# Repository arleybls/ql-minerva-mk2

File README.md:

# Sinclair QL - Minerva MK II Reimagined (SMD edition)

A surface-mount redesign of the Minerva MK II ROM and clock board for the Sinclair QL, based on
[Alvaro Alea Fernandez's KiCad recreation](https://github.com/alvaroalea/QL_Minerva_MK2) of the
original 1990 QView board.

The board plugs into the QL's internal ROM socket. It replaces the QL's ROM with a 64 KB EPROM
holding the Minerva operating system, with Toolkit II in the upper 16 KB if you want it, and adds
a battery-backed PCF8583 real-time clock. The clock sits on an I2C port inside the ROM address
space, so the QL reads it with ordinary ROM reads.

Left: the assembled board. Right: with the I2C cable plugged into J2.

## What is different from Alvaro's board

| | Alvaro's board | This board |
|---|---|---|
| Construction | through-hole | surface mount, 42.7 x 40.6 mm, two layers, ground pour on each side |
| EPROM | W27C512, DIP-28 socket, with the 74LS133 soldered underneath it | 27C512 in a PLCC-32 SMD socket; nothing mounted under anything |
| GAL16V8 | DIP-20 socket | PLCC-20 SMD socket, still reprogrammable |
| 13-input NAND | 74LS133, DIP-16 | SN74ALS133, SOP-16 |
| Resistors, diode, crystal, trimmer | axial, DO-35, AT310, radial trimmer | 0603, SOD-123W, FC-135, TZC3 SMD trimmer |
| Expansion header J2 | 2.54 mm pins | PicoBlade 53261 |
| Battery | external, through a two-pin header and a 120 ohm trickle-charge resistor | CR927 coin cell on the board, fed through two Schottky diodes so the cell is never charged and takes over when the QL is off |
| GAL pins 6 and 7 | pin 6 on VCC, pin 7 on /DECODE | pin 6 on SW1, pin 7 on +5 V, as the MINGAL_MH v1.10 equations require; this makes the map-in/map-out of the upper 16 KB work |
| Upper 16 KB select | JP1 solder jumper | SW1 slide switch (see below) |
| Decoupling | two capacitors | four 100 nF: at the GAL, the 74ALS133 and the EPROM on +5 V, and one at the PCF8583 on the battery rail |
| Clock chip testing | none | a small tester board and sketch (see below) |

### A switch instead of a solder jumper

Upstream JP1 was a three-pad solder jumper with its centre pad on the /DECODE net, which is the
74LS133's output. Pads 1 and 2 were bridged by default, so the jumper shorted that output to the
supply. SW1, a slide switch on its own GAL input, replaces it. SW1 selects whether the EPROM's
upper 16 KB (Toolkit II) is mapped in or left free for an external expansion ROM.

### A tester for the clock chips

`pcf8583-tester/` is a small separate board (Arduino Nano plus a DIP-8 socket) and a sketch for
checking PCF8583 chips before one is soldered in. It writes ten test patterns to all 248 bytes
of RAM, checks the clock registers, then drives the chip's oscillator input from the Nano at 100
times real speed to run the whole counter chain: minute, hour, month, leap-year rollovers, the
alarm and the timer. It prints a checklist and a pass or fail verdict in about three seconds.
Second-hand and old-stock PCF8583s vary a lot in quality, and this finds the bad ones. See
[pcf8583-tester/README.md](pcf8583-tester/README.md).

## Repository layout

```
QL_Minerva_MK2.kicad_sch / .kicad_pcb / .kicad_pro   the board (KiCad 10)
gerber/                                              fabrication files for the current board
bom/ibom.html                                        interactive BOM
images/                                              photos
pcf8583-tester/                                      clock chip tester: KiCad project, gerbers, sketch, README
```

The ROM image and the GAL files are not in this repository. They are the work of their
original authors; the next two sections say where to get them and how to prepare them.

## Getting the GAL code

The GAL16V8 needs the MINGAL_MH v1.10 fuse map (`MINGAL_MH_v110.jed`). Alvaro's README says
where his copy came from:

> Main information, GAL code, pictures, etc... has been obtained from this post:
> https://qlforum.co.uk/viewtopic.php?t=1993

That thread on qlforum.co.uk has the JEDEC file, the equations and the history of the v1.00
and v1.10 versions. Program the `.jed` into a GAL16V8 (or an ATF16V8) with any GAL programmer,
for example a TL866 with minipro or Xgpro.

## Building the ROM image with Toolkit II

The 27C512 holds a 1:1 image of the QL's ROM area:

```
0x0000-0xBFFF   Minerva 1.98a1 operating system (48 KB)
0xC000-0xFFFF   Toolkit II 2.36 (16 KB), in the QL's expansion ROM slot
```

The 64 KB image is nothing more than the two files joined, Minerva first.

1. Get Minerva 1.98a1 (the 48 KB ROM file) from Tony Firshman's Minerva page:
   http://tfs.firshman.co.uk/ql/minerva.htm
2. Get the Toolkit II v2.36 ROM image (16 KB) from Dilwyn Jones' site:
   https://dilwyn.qlforum.co.uk/docs/manuals/index.html (Toolkit II section).
3. Check the sizes: Minerva must be exactly 49,152 bytes and Toolkit II 16,384 bytes.
   If the Toolkit II file is shorter, pad it with 0xFF to 16,384 bytes.
4. Join them.

   Linux or macOS:

   ```
   cat Minerva_1.98a1.bin TK2_2.36.rom > Minerva_1.98a1_plus_TK2_2.36.bin
   ```

   Windows (PowerShell):

   ```
   cmd /c copy /b Minerva_1.98a1.bin+TK2_2.36.rom Minerva_1.98a1_plus_TK2_2.36.bin
   ```

   The result must be exactly 65,536 bytes.
5. Burn the 64 KB file into the 27C512 and set SW1 so the upper 16 KB is mapped in.

If you do not want Toolkit II, burn the 48 KB Minerva file on its own (the programmer fills the
rest of the EPROM with 0xFF) and set SW1 so the upper 16 KB is left free for an expansion ROM.

The last four bytes of the Minerva image (0xBFDC-0xBFDF) are the clock's I2C window. The GAL
intercepts reads there, so whatever the EPROM holds at those addresses is never seen; Minerva
reserves them for this purpose.

## Building one

1. Order the board from `gerber/`.
2. Fit the SMD parts, the two PLCC sockets and the CR927 holder. U1 is a 28-pin header row
   mounted on the solder side so the board can be plugged into the QL's ROM socket.
3. Program a GAL16V8 with `MINGAL_MH_v110.jed` and a 27C512 with the Minerva image, with or
   without Toolkit II (see the two sections above).
4. If the PCF8583 is not a new part, run it through the tester first, then fit it.
5. Set SW1: Toolkit II mapped in (64 KB image), or upper 16 KB left free for an expansion ROM.
6. Fit the cell, plug the board into the QL's ROM socket and power up.

## Licence

CERN Open Hardware Licence Version 2, Strongly Reciprocal (CERN-OHL-S v2), the same licence
as Alvaro's repository. The full text is in [LICENSE](LICENSE). The Minerva MK II design, the
Minerva OS and the GAL equations remain the work of their original authors. This repository
only carries the redesigned board.

Board redesign and tester (c) 2026 Arley Silveira. KiCad capture of the original (c) 2024
Alvaro Alea Fernandez.

Source location: https://github.com/arleybls/ql-minerva-mk2

Modification notice (CERN-OHL-S 3.3b): in 2025-2026 Arley Silveira converted Alvaro Alea
Fernandez's through-hole design to surface mount, added the on-board battery, rewired GAL pins
6 and 7, replaced JP1 with SW1, added decoupling and wrote the PCF8583 tester.

## References

- Alvaro's repository: https://github.com/alvaroalea/QL_Minerva_MK2
- Minerva at Tony Firshman's site: http://tfs.firshman.co.uk/ql/minerva.htm
- Minerva on the QL wiki: https://wiki.qlforum.co.uk/doku.php?id=qlwiki:minerva
- Manuals and software: https://dilwyn.qlforum.co.uk/docs/manuals/index.html
- Minerva MK II forum thread with the GAL code, pictures and history: https://qlforum.co.uk/viewtopic.php?t=1993

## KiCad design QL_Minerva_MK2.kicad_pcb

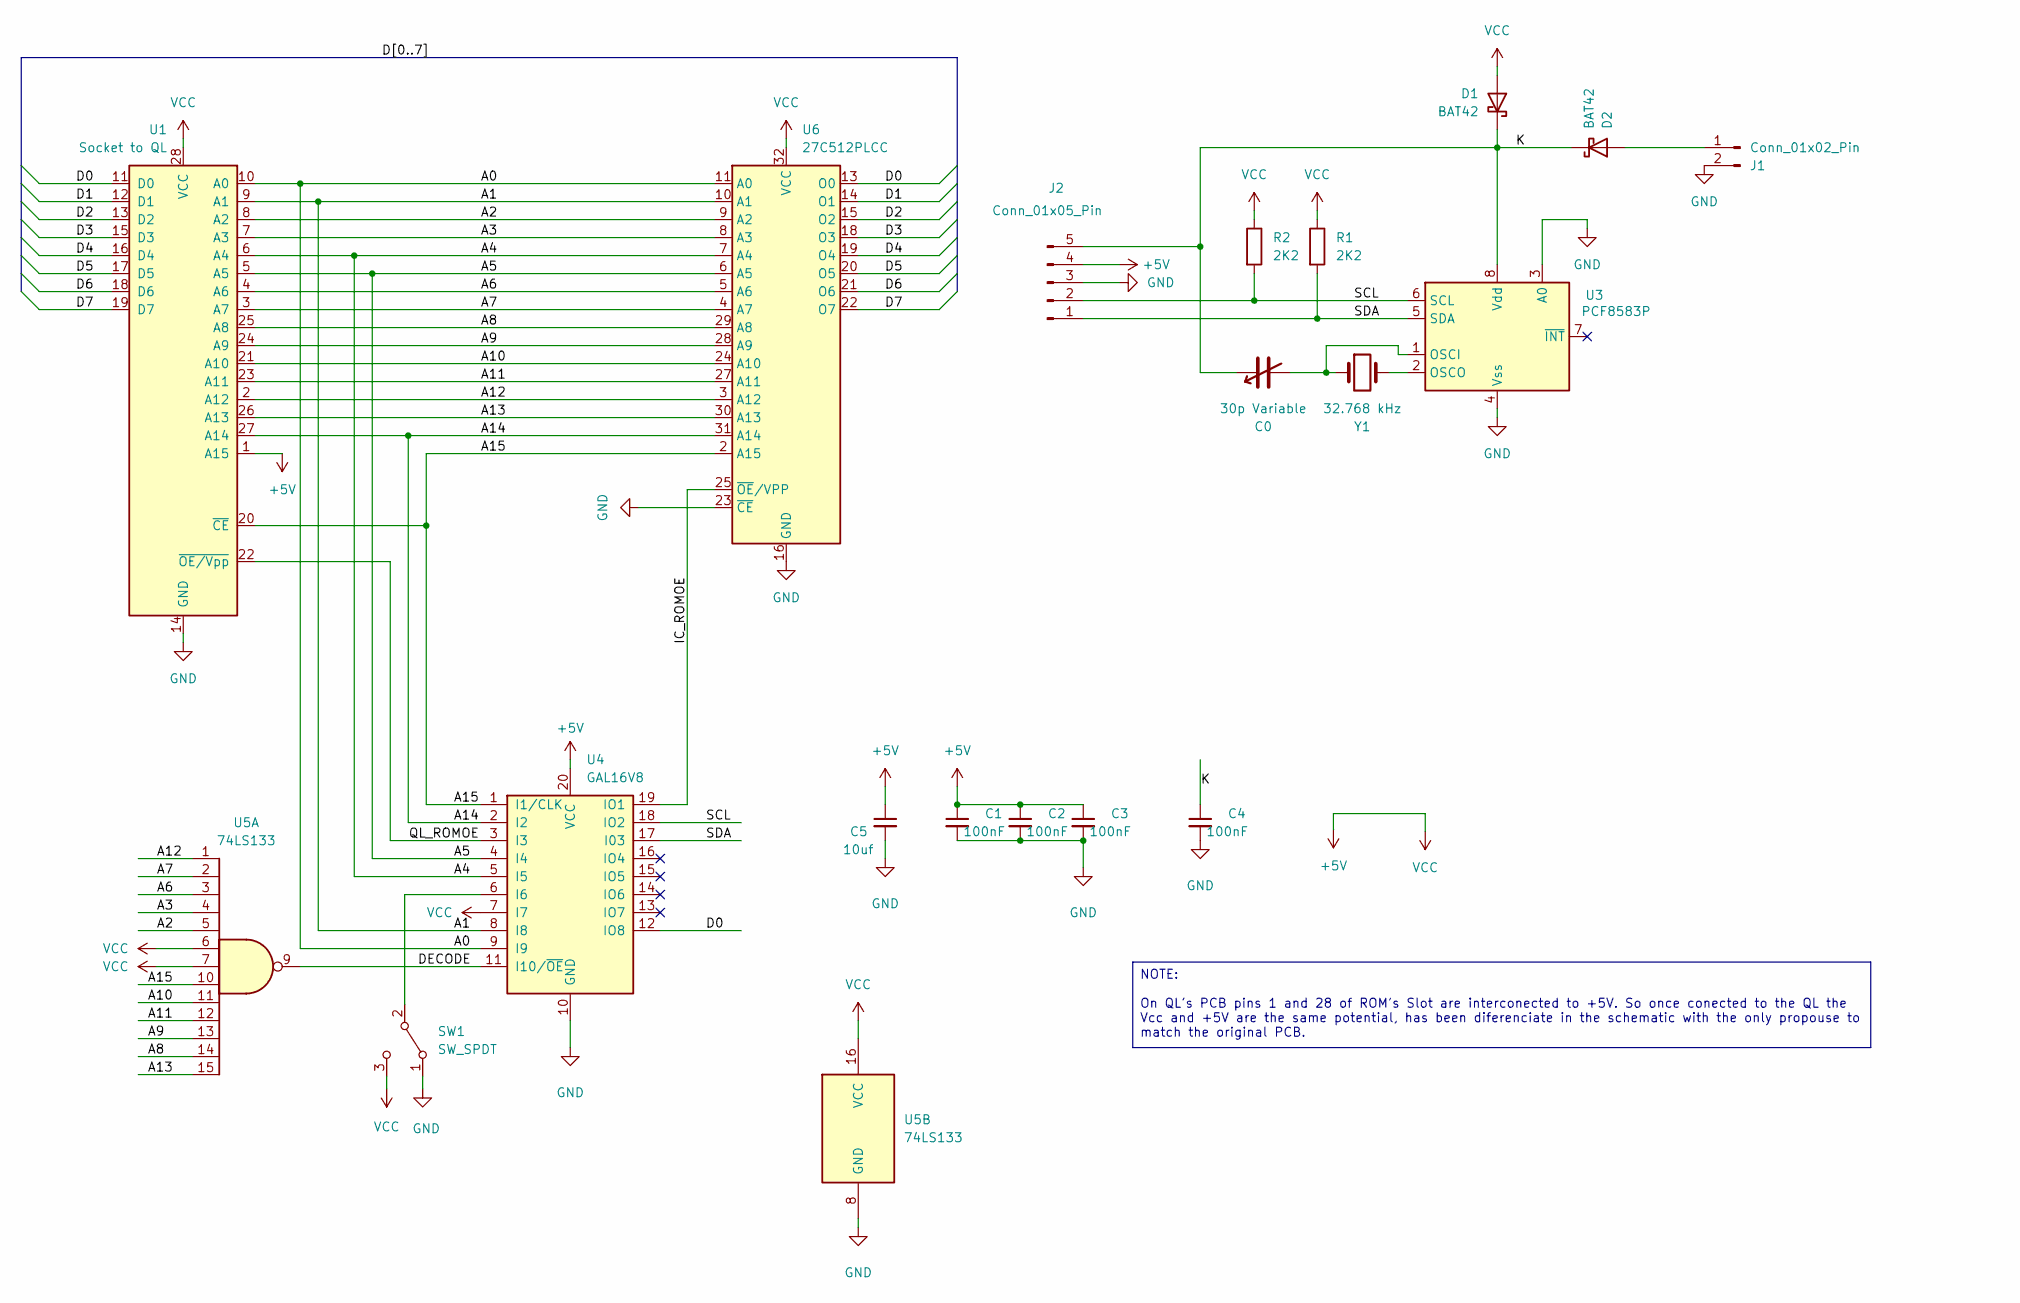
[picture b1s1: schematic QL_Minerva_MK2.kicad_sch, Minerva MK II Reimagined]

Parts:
C0: 30p Variable; TZC3_MUR
C1, C2, C3, C4: 100nF; C_0603_1608Metric
C5: 10uf; C_0805_2012Metric
D1: BAT42; Nexperia_CFP3_SOD-123W
D2: BAT42; BAT42WS
J1: Conn_01x02_Pin; CR927Holder
J2: Conn_01x05_Pin; PicoBlade_53261
R1, R2: 2K2; R_0603_1608Metric
SW1: SW_SPDT; SW_SPDT_PCM12
U1: Socket to QL; DIP-28_W15.24mm
U3: PCF8583P; DIP-8_W7.62mm
U4: GAL16V8; PLCC-20_SMD-Socket
U5: 74LS133; SN74ALS133NSR
U6: 27C512PLCC; CONN_PLCC-32-AT-SMT_ADM
Y1: 32.768 kHz; XTAL_FC-135_32.7680KA-A0

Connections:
+5V: C1.1, C2.1, C3.1, C5.1, D1.2 (A), J2.4, R1.1, R2.1, SW1.3 (C), U1.1 (A15), U1.28 (VCC), U4.7 (I7), U4.20 (VCC), U5.6, U5.7, U5.16 (VCC), U6.32 (VCC)
/A0: U1.10 (A0), U4.9 (I9), U6.11 (A0)
/A1: U1.9 (A1), U4.8 (I8), U6.10 (A1)
/A2: U1.8 (A2), U5.5, U6.9 (A2)
/A3: U1.7 (A3), U5.4, U6.8 (A3)
/A4: U1.6 (A4), U4.5 (I5), U6.7 (A4)
/A5: U1.5 (A5), U4.4 (I4), U6.6 (A5)
/A6: U1.4 (A6), U5.3, U6.5 (A6)
/A7: U1.3 (A7), U5.2, U6.4 (A7)
/A8: U1.25 (A8), U5.14, U6.29 (A8)
/A9: U1.24 (A9), U5.13, U6.28 (A9)
/A10: U1.21 (A10), U5.11, U6.24 (A10)
/A11: U1.23 (A11), U5.12, U6.27 (A11)
/A12: U1.2 (A12), U5.1, U6.3 (A12)
/A13: U1.26 (A13), U5.15, U6.30 (A13)
/A14: U1.27 (A14), U4.2 (I2), U6.31 (A14)
/A15: U1.20 (~CE), U4.1 (I1/CLK), U5.10, U6.2 (A15)
/D0: U1.11 (D0), U4.12 (IO8), U6.13 (O0)
/D1: U1.12 (D1), U6.14 (O1)
/D2: U1.13 (D2), U6.15 (O2)
/D3: U1.15 (D3), U6.18 (O3)
/D4: U1.16 (D4), U6.19 (O4)
/D5: U1.17 (D5), U6.20 (O5)
/D6: U1.18 (D6), U6.21 (O6)
/D7: U1.19 (D7), U6.22 (O7)
/DECODE: U4.11 (I10/~OE), U5.9
/IC_ROMOE: U4.19 (IO1), U6.25 (~OE/VPP)
/K: C0.1, C4.1, D1.1 (K), D2.1 (K), J2.5, U3.8 (Vdd)
/QL_ROMOE: U1.22 (~OE/Vpp), U4.3 (I3)
/SCL: J2.2, R2.2, U3.6 (SCL), U4.18 (IO2)
/SDA: J2.1, R1.2, U3.5 (SDA), U4.17 (I03)
GND: C1.2, C2.2, C3.2, C4.2, C5.2, J1.2, J2.3, SW1.1 (A), U1.14 (GND), U3.3 (A0), U3.4 (Vss), U4.10 (GND), U5.8 (GND), U6.16 (GND), U6.23 (~CE)
unnamed: D2.2 (A), J1.1
unnamed: SW1.2 (B), U4.6 (I6)
unnamed: C0.2, U3.1 (OSCI), Y1.1
unnamed: U3.2 (OSCO), Y1.2

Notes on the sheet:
NOTE: On QL's PCB pins 1 and 28 of ROM's Slot are interconected to +5V. So once conected to the QL the Vcc and +5V are the same potential, has been diferenciate in the schematic with the only propouse to match the original PCB.

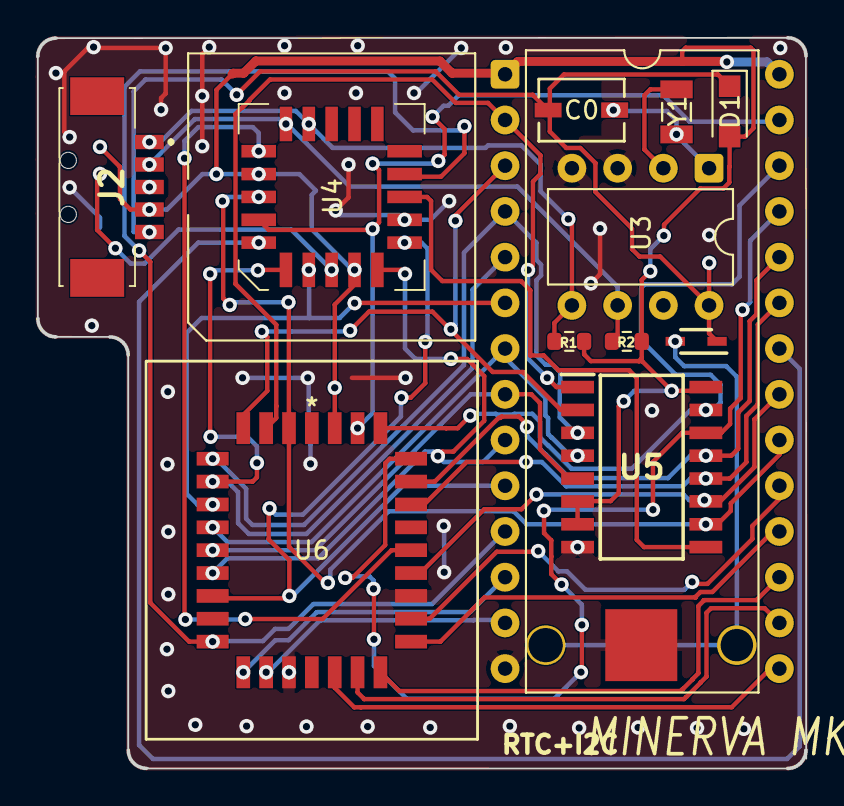
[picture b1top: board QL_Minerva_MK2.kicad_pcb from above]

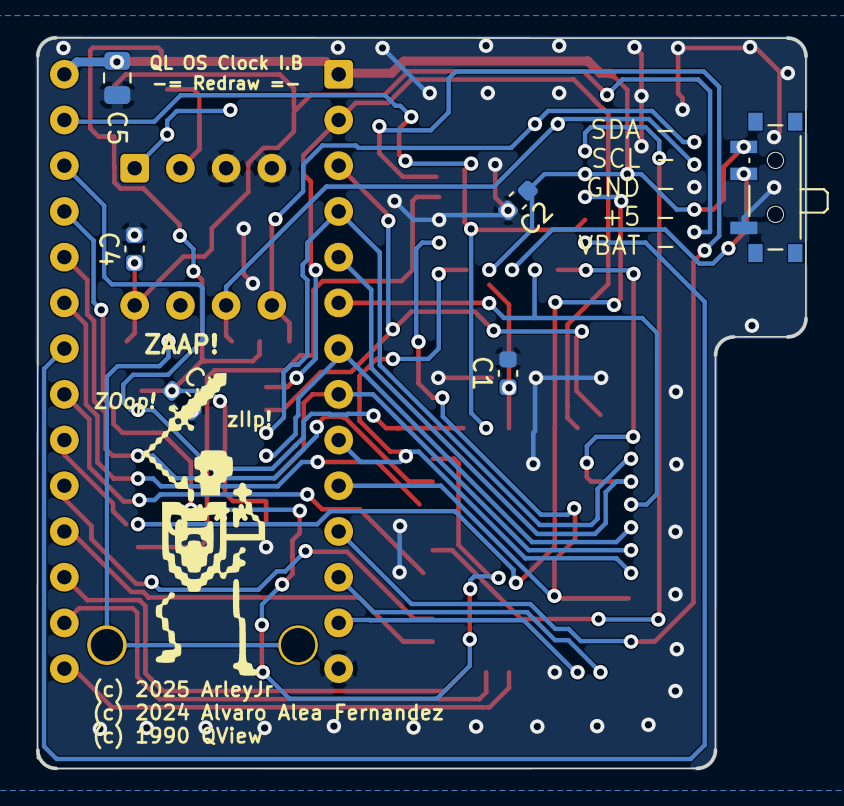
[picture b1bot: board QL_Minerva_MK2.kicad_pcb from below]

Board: 2 copper layers, 42.7 x 40.6 mm, 19 parts (6 on the bottom side), 36 nets.

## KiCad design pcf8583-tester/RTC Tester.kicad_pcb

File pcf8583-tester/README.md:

# PCF8583 tester

Go/no-go tester for PCF8583 real-time-clock/RAM chips, built to screen chips
before fitting one to the QL Minerva MK2 board.

Insert a chip in the socket, the test runs by itself and prints a checklist and
a verdict on the serial port. Remove the chip, insert the next one.

## Contents

| Path | What |
|---|---|
| `RTC Tester.kicad_sch` / `.kicad_pcb` / `.kicad_pro` | KiCad 9 project: Arduino Nano, DIP-8 socket for the PCF8583, two 2.2 kΩ I2C pull-ups |
| `gerbers/` | Fabrication files for the board above |
| `pcf8583-tester-sketch/pcf8583-tester-sketch.ino` | Arduino sketch |

## Hardware

Board as designed:

| PCF8583 pin | Net |
|---|---|
| 1 OSCI | not connected |
| 2 OSCO | not connected |
| 3 A0 | not connected |
| 4 VSS | GND |
| 5 SDA | Nano A4, 2.2 kΩ to +5 V |
| 6 SCL | Nano A5, 2.2 kΩ to +5 V |
| 7 INT | not connected |
| 8 VDD | +5 V |

Two bodge wires are needed on the current board revision:

1. **A0 to VSS** — socket pin 3 to pin 4. Without it A0 floats, the chip's
   I2C address flickers between 0x50 and 0x51 and results are unreliable.
2. **Nano D9 to OSCI** — socket pin 1. The Nano generates the clock that
   drives the chip's counter chain (see *Driven tests* below). Optional: without
   it set `HAS_OSC_DRIVE` to 0 and the driven tests are skipped.

There is no crystal and no battery on this board, so the chip's own oscillator
and battery retention are not tested. See *Limits*.

## Flashing the Nano

Arduino IDE 2:

1. Open `pcf8583-tester-sketch/pcf8583-tester-sketch.ino`.
2. Tools → Board → Arduino AVR Boards → **Arduino Nano**.
3. Tools → Processor → **ATmega328P (Old Bootloader)** for a clone Nano
   (plain **ATmega328P** for a genuine one; switch if upload reports "not in sync").
4. Tools → Port → the Nano's COM port.
5. Upload.

Or with `arduino-cli`:

```
arduino-cli compile --upload --fqbn arduino:avr:nano:cpu=atmega328old -p COMx pcf8583-tester-sketch
```

Only the built-in `Wire` library is used.

## Using it

1. Open the Serial Monitor at **115200 baud**. You should see:

   ```
   PCF8583 tester - insert chip
   (HAS_CRYSTAL=0: oscillator test disabled on this board)
   (OSCI driven from D9 at 5000 Hz = 100x real time)
   ```

   While no chip is present a `.` is printed every 5 s as a heartbeat.

2. Insert a chip, pin 1 towards the socket notch. The test starts within
   0.5 s and takes about 3 s. Output:

   ```
   === chip detected at 0x50 ===
   progress [######################################] done

     [✓] i2c     bus detection  -> ACK at 0x50 (A0 low)
     [✓] 0x00    uniform pattern
     [✓] 0xFF    uniform pattern
     [✓] 0x55    uniform pattern
     [✓] 0xAA    uniform pattern
     [✓] walk1   walking 1, bit coupling
     [✓] walk0   walking 0, bit coupling
     [✓] addr    address in cell, aliasing
     [✓] ~addr   inverse address in cell
     [✓] hash    pseudo-random pattern
     [✓] hold    data hold 2 s
     [✓] clkreg  clock regs 0x01-0x07 as RAM
     [✓] wrap    address wrap 0xFF -> 0x00
     [✓] date    set date/time, counter running  -> read back 30/08 y+2 wd6 12:34:56
     [✓] roll    rollovers: min/hour/month/leap/year
     [✓] alarm   daily alarm flag
     [✓] timer   timer counts seconds
     [-] TIME    seconds advance  -> not tested (no crystal on this board)
     [✓] clean   chip zeroed

   CHIP @0x50: PASS (18 tests, oscillator not tested)
   ```

   followed by a large "passed!" banner. A failing chip prints
   `CHIP @0x50: FAIL (n of 18 tests failed)` instead, with details on the
   failing rows (see *Reading failures*).

3. Remove the chip. The tester prints `insert next chip` and re-arms.

The chip is hot-plugged with the Nano powered. That is normally harmless for
this CMOS part; if you prefer, power the Nano off between chips — the test
runs on power-up the same way.

## What is tested

The chip's memory map: 0x00 control/status, 0x01–0x07 clock counters,
0x08–0x0F alarm registers, 0x10–0xFF 240 bytes free RAM. Everything from 0x08
up is tested as RAM (the Minerva ROM may use the alarm area as storage).

### I2C

| Row | Check |
|---|---|
| `i2c` | Chip ACKs at 0x50 (A0 low) or 0x51 (A0 high). Answering at **both** is a fault: A0 floating or the chip's A0 input broken. The address found is reported. |

Every read and write in every test checks the I2C result. A NAK or short read
marks that test `BUS ERROR @0x..`, and the remaining tests are skipped, so a
bus problem can never be mistaken for a memory fault.

### RAM march, 0x08–0xFF (248 bytes)

Each pass writes the whole range then reads it all back.

| Row | Pattern | Catches |
|---|---|---|
| `0x00` `0xFF` `0x55` `0xAA` | uniform | stuck bits, shorted adjacent bits |
| `walk1` | one bit set per byte, rotating with address | bit-to-bit coupling within a byte |
| `walk0` | one bit cleared per byte, rotating | same, opposite polarity |
| `addr` | each cell holds its own address | address-line faults: two addresses hitting one cell |
| `~addr` | inverse of its address | same, opposite polarity |
| `hash` | pseudo-random function of the address | pattern-sensitive cells |
| `hold` | the `hash` pattern re-read after 2 s | cells that leak |

### Registers

| Row | Check |
|---|---|
| `clkreg` | 0x01–0x07 written with 0x55/0xAA patterns and read back while the counter is stopped (control bit 7). |
| `wrap` | A 2-byte read starting at 0xFF must return 0xFF then 0x00 (control register): the address auto-increment wraps. |
| `date` | Control = 0x00 (clock mode, running), the way the Minerva ROM uses it. Writes 30 August, year+2, Sunday, 12:34:56 in the datasheet register layouts, waits 300 ms, reads everything back and checks every field. The decoded read-back is printed. |

### Driven tests (`HAS_OSC_DRIVE`)

The PCF8583 has a "50 Hz" mode (control bits 5:4 = 01) that clocks the counter
chain from an external signal on OSCI instead of the crystal. The Nano drives
OSCI at 5 kHz with `tone()`, so the clock runs at 100× real time: one chip
second is 10 ms. This exercises every part of the RTC logic except the crystal
oscillator itself.

| Row | Check |
|---|---|
| `roll` | Seven rollover cases. Each sets the clock at hh:mm:58 plus a date, waits 2.5 chip-seconds, and checks minutes, hours, date, month, weekday and year: |

| Case | Set | Expect |
|---|---|---|
| 1 | 12:34:58 | 12:35 |
| 2 | 12:59:58 | 13:00 |
| 3 | 23:59:58 30 Apr | 00:00 01 May, weekday +1 |
| 4 | 23:59:58 31 May | 01 Jun |
| 5 | 23:59:58 28 Feb, year+1 | 01 Mar (non-leap) |
| 6 | 23:59:58 28 Feb, year+0 | 29 Feb (the chip's year 0 is the leap year) |
| 7 | 23:59:58 31 Dec, year+3 | 01 Jan, year+0 (year counter wraps) |

| Row | Check |
|---|---|
| `alarm` | Clock 12:34:58, daily alarm 12:35:00, alarm enabled. The alarm flag must be clear right after arming and set 3.5 chip-seconds later. |
| `timer` | Timer function = seconds, timer register = 00. Must read 03 or 04 after 3.5 chip-seconds. |

### Oscillator (`HAS_CRYSTAL`)

| Row | Check |
|---|---|
| `TIME` | Only with a crystal fitted: set 12:34:56 in normal 32.768 kHz mode, wait 2.5 s, seconds must have advanced. Shown as `[-] not tested` on this board. |

### Cleanup

| Row | Check |
|---|---|
| `clean` | 0x01–0xFF zeroed and control register set to 0x00, so a passing chip goes into a Minerva blank. Counts as a test because it is a final write pass. |

## Reading failures

Each failing row prints the first mismatch:

```
  [✗] addr    address in cell, aliasing  -> FAIL @0x41 expected 0x41 got 0x40 bad bits 0x01, 12 bytes
```

* `@0x41` — register address of the first bad byte.
* `bad bits` — XOR of expected and actual: which bits are wrong.
* `12 bytes` — total bad bytes in that pass.

For `roll` the address is replaced by the case number and register:

```
  [✗] roll    rollovers: min/hour/month/leap/year  -> FAIL case 6 reg 0x05 expected 0x29 got 0x01
```

(case 6 = leap-year February, register 0x05 = year/date; here the chip treated
year 0 as non-leap.)

Rules of thumb:

* Same bit wrong across many addresses → stuck data line or bad output driver.
* `addr` / `~addr` fail while the uniform patterns pass → address decoding fault.
* Only `hold` fails → leaky cells; the chip may work but will not keep data on
  battery.
* `BUS ERROR` mid-run on a chip that was detected → poor socket contact, or the
  A0 bodge is missing and the address flickered. Re-seat and retry before
  blaming the chip.
* `i2c` reports 0x51 → chip works but A0 is high: the bodge is missing.

## Configuration

At the top of the sketch:

| Define | Default | Meaning |
|---|---|---|
| `HAS_CRYSTAL` | 0 | 1 on a board with a 32.768 kHz crystal: enables `TIME` and lets `date` tolerate ticking seconds |
| `HAS_OSC_DRIVE` | 1 | 1 with the D9→OSCI wire: enables `roll`, `alarm`, `timer` |
| `OSC_PIN` | 9 | Nano pin driving OSCI |
| `OSC_HZ` | 5000 | drive frequency; speed-up factor is `OSC_HZ / 50` |
| `HOLD_MS` | 2000 | wait for the `hold` pass |
| `CHUNK` | 16 | bytes per I2C transaction (Wire buffer is 32) |

Serial is 115200 baud, I2C 100 kHz (the PCF8583 maximum).

## Limits

A PASS here means: good RAM, good I2C interface, good counter/calendar/alarm
logic. It does **not** prove:

* the on-chip oscillator amplifier works with a real crystal (`TIME`, needs a
  crystal on the board);
* the chip keeps time and RAM on battery (needs a battery and a retention test).

Both are planned for a board revision with a 32.768 kHz crystal, trimmer, A0
tied to ground and a backup battery with diode.

## History

The first version of this sketch tested a single RAM byte at a hard-coded
address 0x50 without checking I2C results. With A0 floating on the board, the
chip's address drifted between 0x50 and 0x51 and good chips were reported as
bad. If you have chips rejected by that version, re-test them.

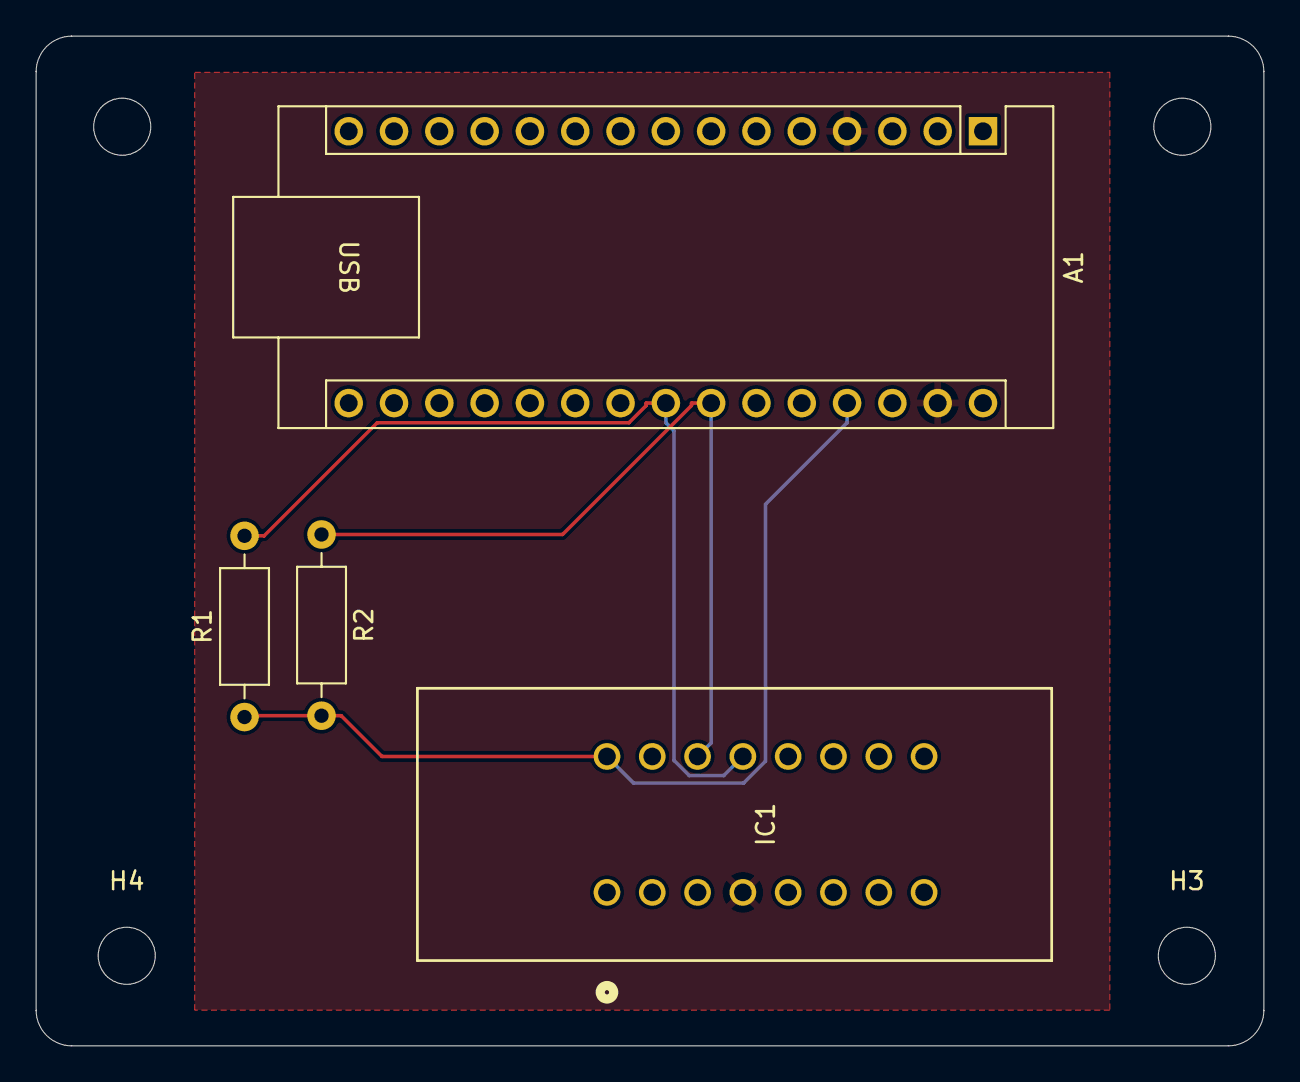
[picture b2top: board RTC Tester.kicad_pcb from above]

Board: 2 copper layers, 68.8 x 56.6 mm, 8 parts (0 on the bottom side), 4 nets.

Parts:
A1: Arduino_Nano_v3.x; Arduino_Nano
H1, H2, H3, H4: MountingHole; MountingHole_3.2mm_M3
IC1: PCF8583P_F5,112; ZIF16_TO_PCF8583
R1, R2: 2.2K; R_Axial_DIN0207_L6.3mm_D2.5mm_P10.16mm_Horizontal

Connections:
+5V: A1.27 (+5V), IC1.8 (VDD), R1.1, R2.2
GND: A1.4 (GND), A1.29 (GND), IC1.4 (VSS)
unnamed: A1.23 (A4), IC1.5 (SDA), R1.2
unnamed: A1.24 (A5), IC1.6 (SCL), R2.1

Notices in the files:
QL_Minerva_MK2.kicad_pcb:
Copyright (c) 2026 Arley Silveira - SMD redesign
Based on the KiCad capture (c) 2024 Alvaro Alea Fernandez
Licence: CERN-OHL-S v2
(c) 2025 ArleyJr
(c) 1990 QView
